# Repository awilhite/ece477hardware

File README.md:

# ece477hardware
ECE 477 Hardware

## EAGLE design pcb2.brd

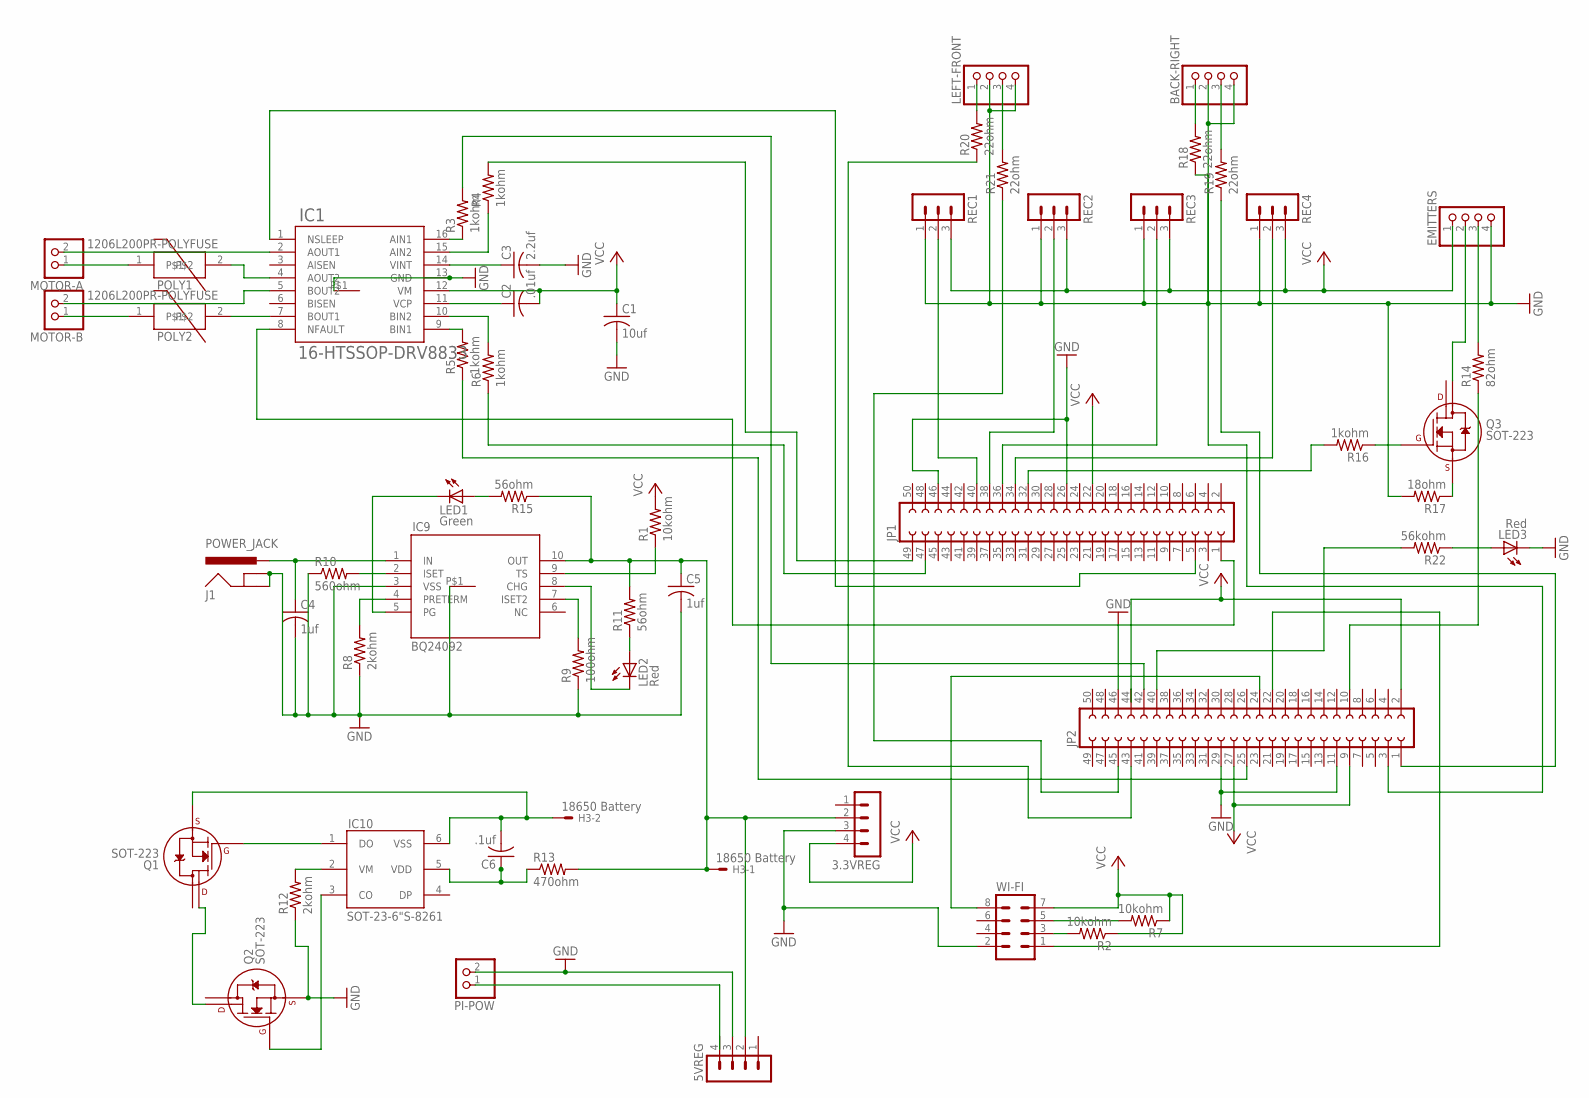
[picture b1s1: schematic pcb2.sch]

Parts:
3.3VREG, 5VREG: MA04-1
BACK-RIGHT: PINHD-1X4; 1X04
C1: 10uf; C0805
C2: .01uf; C0805
C3: 2.2uf; C1206
C4, C5: 1uf; C1206
C6: .1uf; C1206
EMITTERS: PINHD-1X4; 1X04
H3: 18650 Battery; KK-156-2
IC1: 16-HTSSOP-DRV8833; TSSOP16E
IC9: BQ24092; DFN10-3X3
IC10: SOT-23-6"S-8261; SOT23-6
J1: POWER_JACK; POWER_JACK_PTH
JP1, JP2: FE25-2
LED1: Green; CHIPLED_0805
LED2, LED3: Red; CHIPLED_0805
LEFT-FRONT: PINHD-1X4; 1X04
MOTOR-A: PINHD-1X2; 1X02
MOTOR-B: PINHD-1X2; 1X02
PI-POW: PINHD-1X2; 1X02
POLY1, POLY2: 1206L200PR-POLYFUSE; R1206
Q1, Q2, Q3: SOT-223
R1, R2, R7: 10kohm; R0805
R3, R4, R5, R6: 1kohm; R0805
R8: 2kohm; R1206
R9: 100ohm; R0805
R10: 560ohm; R1206
R11, R15: 56ohm; R1206
R12: 2kohm; R0805
R13: 470ohm; R1206
R14: 82ohm; R1206
R16: 1kohm; R1206
R17: 18ohm; R1206
R18, R19, R20, R21: 22ohm; R1206
R22: 56kohm; R0805
REC1, REC2, REC3, REC4: MA03-1
WI-FI: MA04-2

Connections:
GND: 3.3VREG.3, 5VREG.3, BACK-RIGHT.2, BACK-RIGHT.4, C1.2, C3.2, C4.2, C5.2, EMITTERS.4, IC1.13 (GND), IC1.P$1, IC9.3 (VSS), IC9.P$1, J1.GND, J1.GNDBREAK, JP1.26, JP1.46, JP2.11, JP2.29, JP2.46, LED3.C, LEFT-FRONT.2, LEFT-FRONT.4, PI-POW.2, Q2.3 (S), R8.1, R9.1, R10.1, R12.1, R17.2, REC1.1, REC2.1, REC3.1, REC4.1, WI-FI.2
unnamed: C3.1, IC1.14 (VINT)
unnamed: IC10.2 (VM), R12.2
unnamed: C2.1, IC1.11 (VCP)
unnamed: IC1.16 (AIN1), R3.1
unnamed: IC1.15 (AIN2), R4.1
unnamed: IC9.5 (PG), LED1.C
unnamed: LED1.A, R15.2
unnamed: IC9.8 (CHG), LED2.C
unnamed: LED2.A, R11.1
unnamed: IC9.2 (ISET), R10.2
unnamed: IC9.4 (PRETERM), R8.2
unnamed: IC10.1 (DO), Q1.1 (G)
unnamed: C4.1, IC9.1 (IN), J1.PWR
unnamed: IC1.9 (BIN1), R5.2
unnamed: IC10.3 (CO), Q2.1 (G)
unnamed: Q1.4 (D2), Q2.4 (D2)
unnamed: IC9.7 (ISET2), R9.2
unnamed: C6.2, H3.2, IC10.6 (VSS), Q1.3 (S)
unnamed: Q3.1 (G), R16.1
unnamed: IC1.10 (BIN2), R6.2
unnamed: C6.1, IC10.5 (VDD), R13.1
unnamed: JP2.10, R14.1
unnamed: 5VREG.4, PI-POW.1
unnamed: EMITTERS.3, R14.2
unnamed: IC1.2 (AOUT1), MOTOR-A.2
unnamed: JP2.24, WI-FI.8
unnamed: JP1.40, REC1.2
unnamed: JP2.22, WI-FI.1
unnamed: JP2.42, R3.2
unnamed: JP1.49, R4.2
unnamed: JP1.47, R6.1
unnamed: JP2.25, R5.1
unnamed: IC1.4 (AOUT2), POLY1.2
unnamed: IC1.5 (BOUT2), MOTOR-B.2
unnamed: MOTOR-A.1, POLY1.1
unnamed: IC9.9 (TS), R1.1
unnamed: R2.2, WI-FI.3
unnamed: 3.3VREG.2, 5VREG.2, C5.1, H3.1, IC9.10 (OUT), R11.2, R13.2, R15.1
unnamed: R7.2, WI-FI.5
unnamed: JP1.34, REC4.2
unnamed: JP1.36, REC3.2
unnamed: JP1.38, REC2.2
unnamed: EMITTERS.2, Q3.2 (D1)
unnamed: MOTOR-B.1, POLY2.1
unnamed: IC1.7 (BOUT1), POLY2.2
unnamed: JP1.32, R16.2
unnamed: BACK-RIGHT.1, R18.2
unnamed: Q3.3 (S), R17.1
unnamed: BACK-RIGHT.3, R19.2
unnamed: LEFT-FRONT.1, R20.2
unnamed: LEFT-FRONT.3, R21.2
unnamed: JP2.3, R18.1
unnamed: IC1.1 (NSLEEP), JP1.5
unnamed: IC1.8 (NFAULT), JP1.1
unnamed: JP2.40, R22.2
unnamed: JP2.45, R21.1
unnamed: JP2.43, R20.1
unnamed: JP2.1, R19.1
unnamed: LED3.A, R22.1
VCC: 3.3VREG.4, C1.1, C2.2, EMITTERS.1, IC1.12 (VM), JP1.22, JP2.2, JP2.9, JP2.27, JP2.44, R1.2, R2.1, R7.1, REC1.3, REC2.3, REC3.3, REC4.3, WI-FI.7

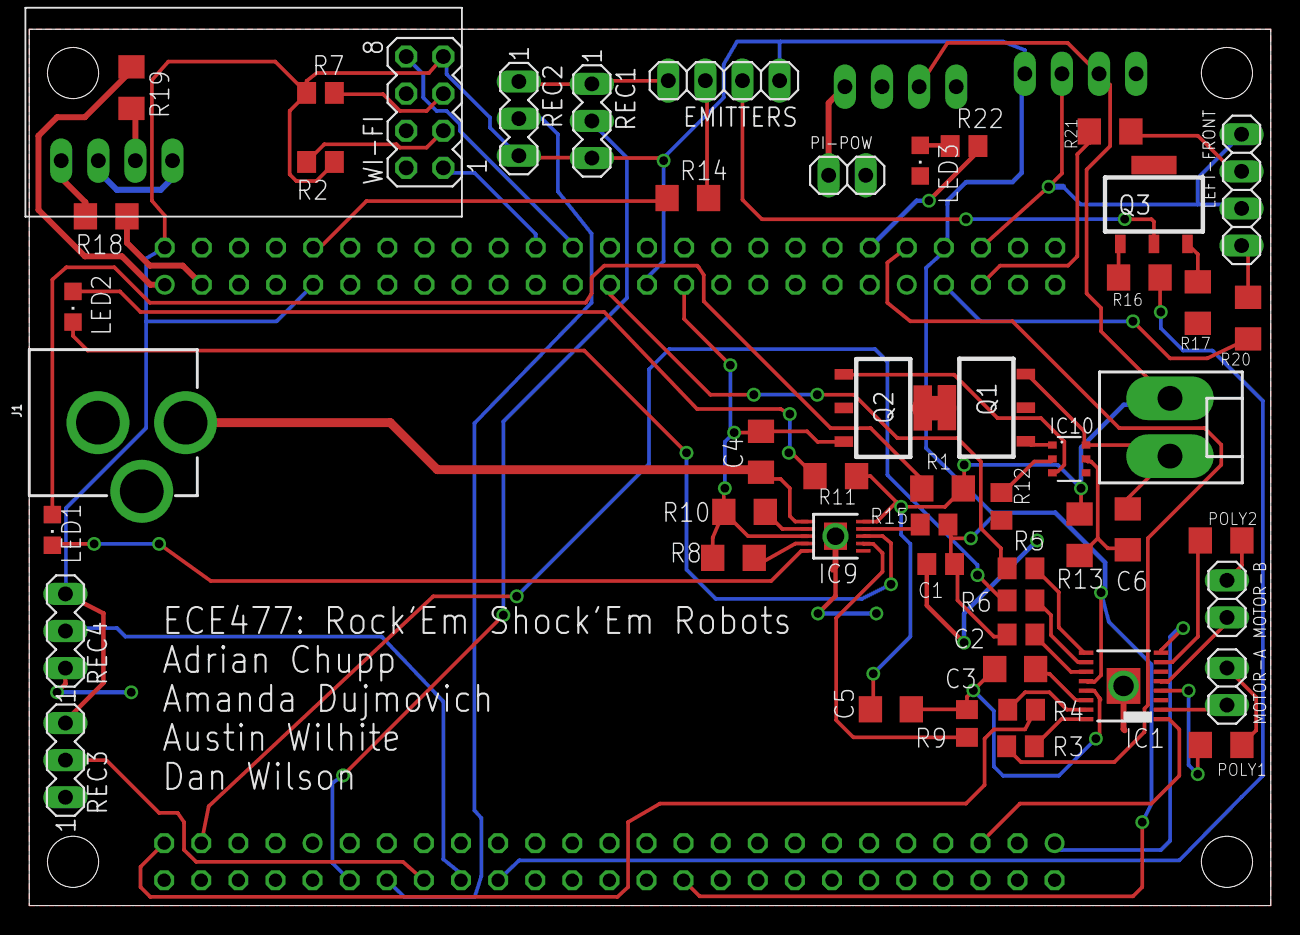
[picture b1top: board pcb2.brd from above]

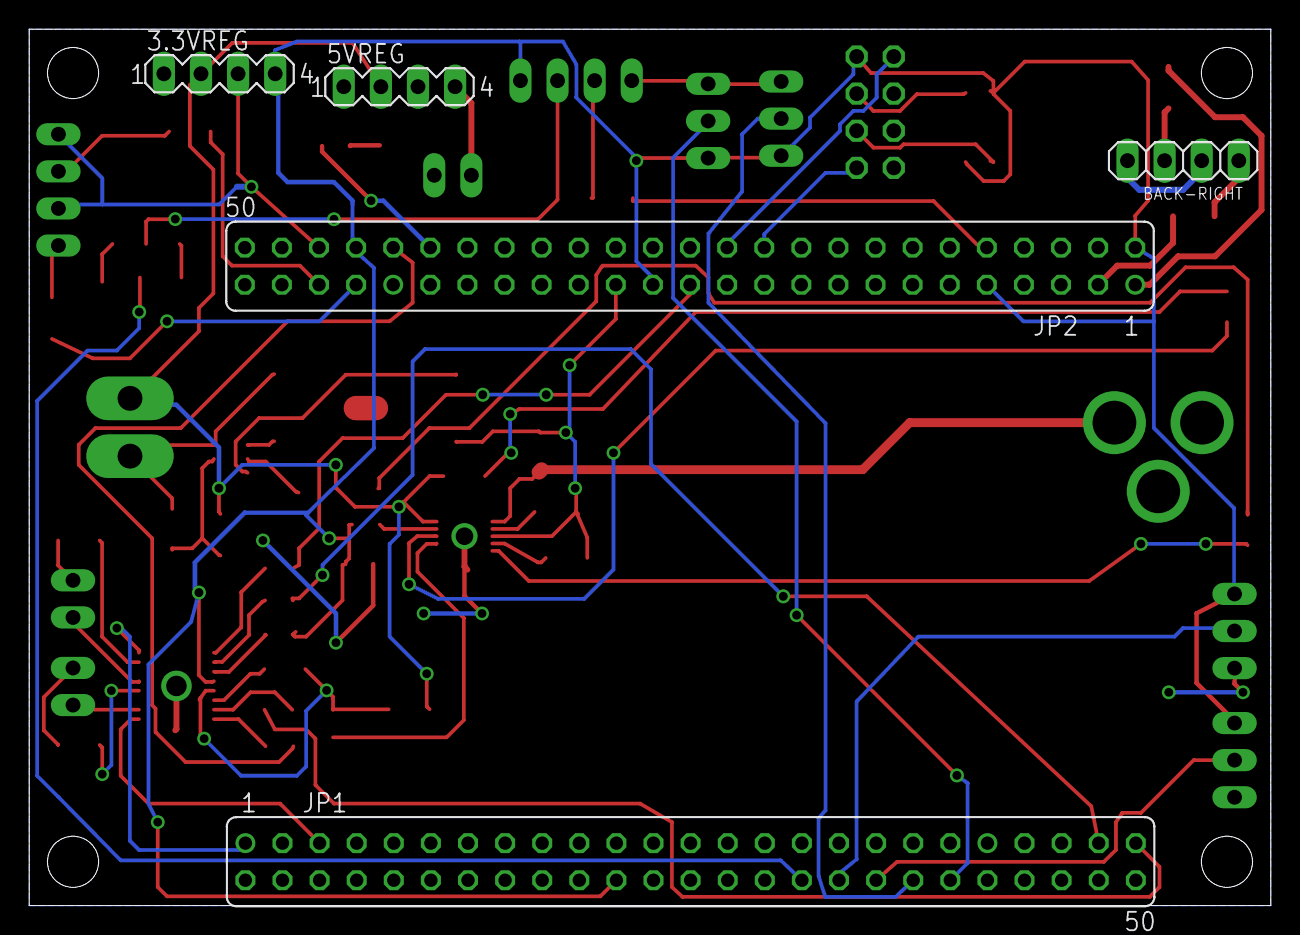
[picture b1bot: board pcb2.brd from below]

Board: 2 copper layers, 85.0 x 60.0 mm, 56 parts (5 on the bottom side), 61 nets.

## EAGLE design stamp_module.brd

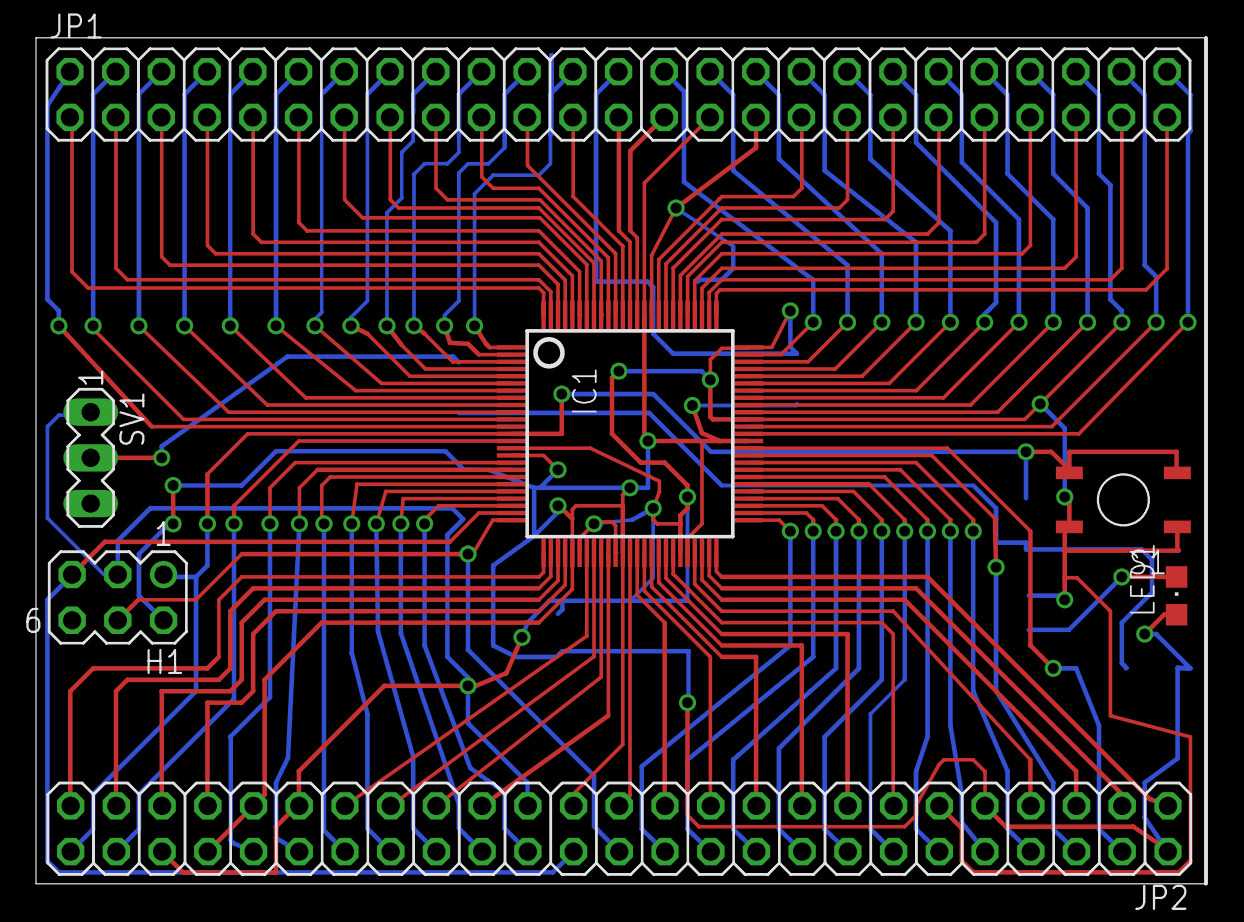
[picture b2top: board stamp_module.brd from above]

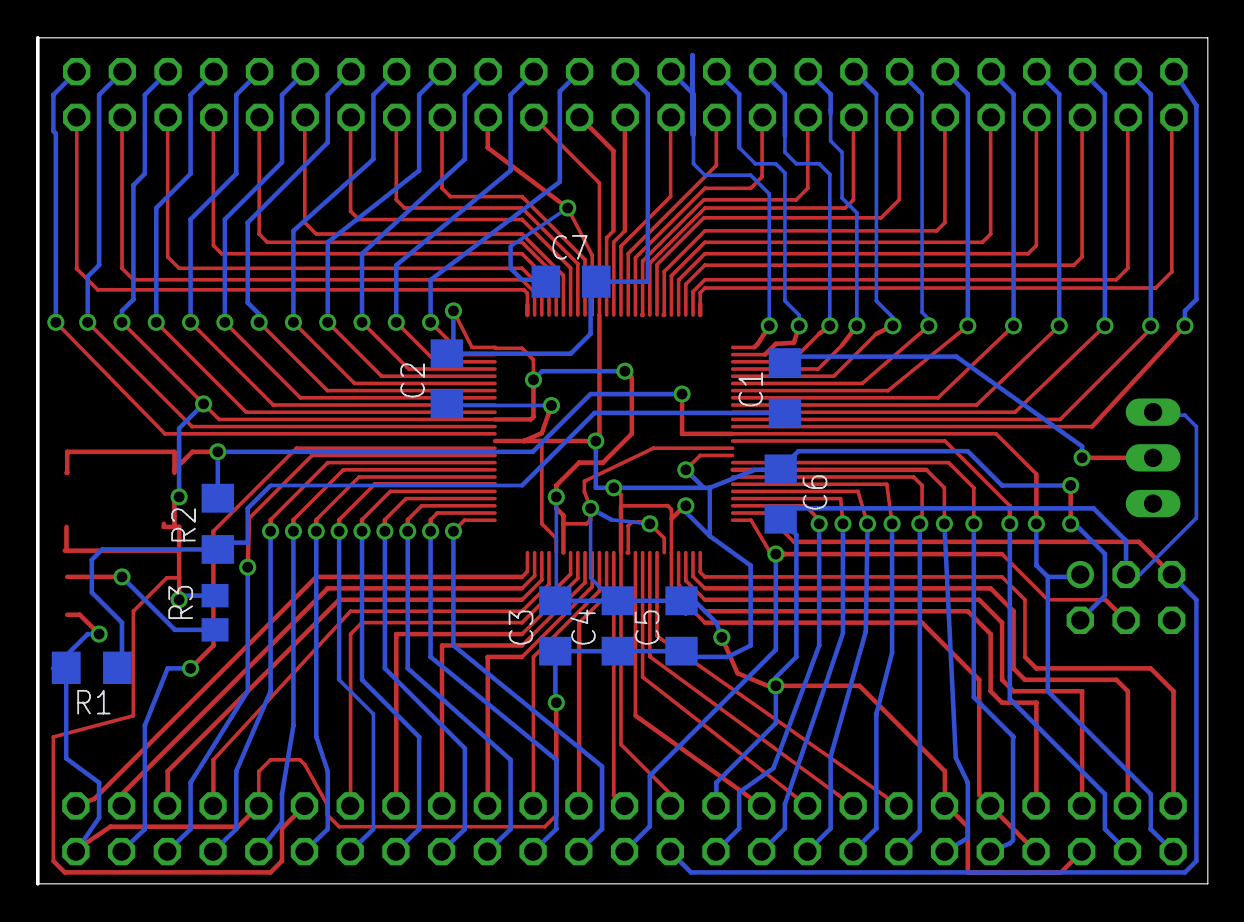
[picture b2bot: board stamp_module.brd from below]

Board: 2 copper layers, 64.9 x 47.0 mm, 17 parts (10 on the bottom side), 93 nets.

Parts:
C1, C2, C3, C4, C5, C6: .1uf; C1206
C7: 10uf; C1206
H1: MA03-2
IC1: PIC24FJ128GA010-12X12; SQFP-S-12X12-100
JP1, JP2: 2X25
LED1: CHIPLED_0805
R1: 10kOhm; R1206
R2: 470Ohm; R1206
R3: 56Ohm; R0805
S1: DTSM-6
SV1: MA03-1

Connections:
GND: C2.2, C3.2, C4.2, C5.2, C6.2, C7.2, H1.3, IC1.15, IC1.31, IC1.36, IC1.45, IC1.65, IC1.75, JP1.26, JP1.46, JP2.11, JP2.29, JP2.39, JP2.46, R3.2, S1.1, S1.2, SV1.1
unnamed: IC1.88, JP1.25
unnamed: C1.2, SV1.2
unnamed: LED1.C, R3.1
unnamed: H1.5, IC1.24, JP2.28
unnamed: H1.1, IC1.13, JP2.50, R2.2, S1.3, S1.4
unnamed: IC1.74, JP1.28
unnamed: IC1.73, JP1.30
unnamed: IC1.72, JP1.32
unnamed: IC1.71, JP1.34
unnamed: IC1.70, JP1.36
unnamed: C1.1, R1.1, R2.1
unnamed: IC1.69, JP1.38
unnamed: IC1.68, JP1.40
unnamed: IC1.67, JP1.42
unnamed: IC1.66, JP1.44
unnamed: H1.4, IC1.25, JP2.26
unnamed: IC1.61, JP2.4
unnamed: IC1.64, JP1.48
unnamed: IC1.63, JP1.50
unnamed: IC1.60, JP2.6
unnamed: IC1.59, JP2.8
unnamed: IC1.58, JP2.10
unnamed: IC1.57, JP2.12
unnamed: IC1.56, JP2.14
unnamed: IC1.55, JP2.16
unnamed: IC1.54, JP2.18
unnamed: IC1.53, JP2.20
unnamed: IC1.52, JP2.22
unnamed: IC1.51, JP2.24
unnamed: IC1.50, JP2.1
unnamed: IC1.49, JP2.3
unnamed: IC1.38, JP2.25
unnamed: IC1.47, JP2.7
unnamed: IC1.44, JP2.13
unnamed: IC1.34, JP2.33
unnamed: IC1.42, JP2.17
unnamed: IC1.41, JP2.19
unnamed: IC1.40, JP2.21
unnamed: IC1.39, JP2.23
unnamed: IC1.48, JP2.5
unnamed: IC1.35, JP2.31
unnamed: IC1.43, JP2.15
unnamed: IC1.33, JP2.35
unnamed: IC1.32, JP2.37
unnamed: IC1.29, JP2.43
unnamed: IC1.28, JP2.45
unnamed: IC1.27, JP2.47
unnamed: IC1.26, JP2.49
unnamed: IC1.4, JP1.18
unnamed: IC1.6, JP1.14
unnamed: IC1.3, JP1.20
unnamed: IC1.2, JP1.22
unnamed: IC1.5, JP1.16
unnamed: IC1.7, JP1.12
unnamed: IC1.8, JP1.10
unnamed: IC1.9, JP1.8
unnamed: IC1.10, JP1.6
unnamed: IC1.11, JP1.4
unnamed: IC1.12, JP1.2
unnamed: IC1.14, JP2.48
unnamed: IC1.17, JP2.42
unnamed: IC1.18, JP2.40
unnamed: IC1.19, JP2.38
unnamed: IC1.20, JP2.36
unnamed: IC1.21, JP2.34
unnamed: IC1.22, JP2.32
unnamed: IC1.23, JP2.30
unnamed: IC1.100, JP1.1
unnamed: IC1.99, JP1.3
unnamed: IC1.98, JP1.5
unnamed: IC1.97, JP1.7
unnamed: IC1.96, JP1.9
unnamed: IC1.95, JP1.11
unnamed: IC1.94, JP1.13
unnamed: IC1.93, JP1.15
unnamed: IC1.92, JP1.17
unnamed: IC1.91, JP1.19
unnamed: IC1.90, JP1.21
unnamed: IC1.89, JP1.23
unnamed: C7.1, IC1.85, JP1.31
unnamed: IC1.87, JP1.27
unnamed: IC1.84, JP1.33
unnamed: IC1.83, JP1.35
unnamed: IC1.82, JP1.37
unnamed: IC1.81, JP1.39
unnamed: IC1.80, JP1.41
unnamed: IC1.79, JP1.43
unnamed: IC1.78, JP1.45
unnamed: IC1.77, JP1.47
unnamed: IC1.76, JP1.49
unnamed: IC1.1, JP1.24
VDD: C2.1, C3.1, C4.1, C5.1, C6.1, H1.2, IC1.16, IC1.30, IC1.37, IC1.46, IC1.62, IC1.86, JP1.29, JP2.2, JP2.9, JP2.27, JP2.41, JP2.44, LED1.A, R1.2

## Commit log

2017-02-15 initial pcb and stamp module schematics
2017-02-23 Preliminary PCB schematic and stamp module layout
2017-02-25 Add files via upload
    Edited Schematic
2017-03-01 Add files via upload
    Final stamp module schematic
2017-03-02 Final schematic
2017-03-02 Final PCB
2017-03-08 Final PCB and schematic

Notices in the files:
parts and their libraries:
SparkFun-Connectors: Licensing: Creative Commons ShareAlike 4.0 International - https://creativecommons.org/licenses/by-sa/4.0
